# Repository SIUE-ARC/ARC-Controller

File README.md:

# ARC-Controller
A PSoC4 based robotics control board.

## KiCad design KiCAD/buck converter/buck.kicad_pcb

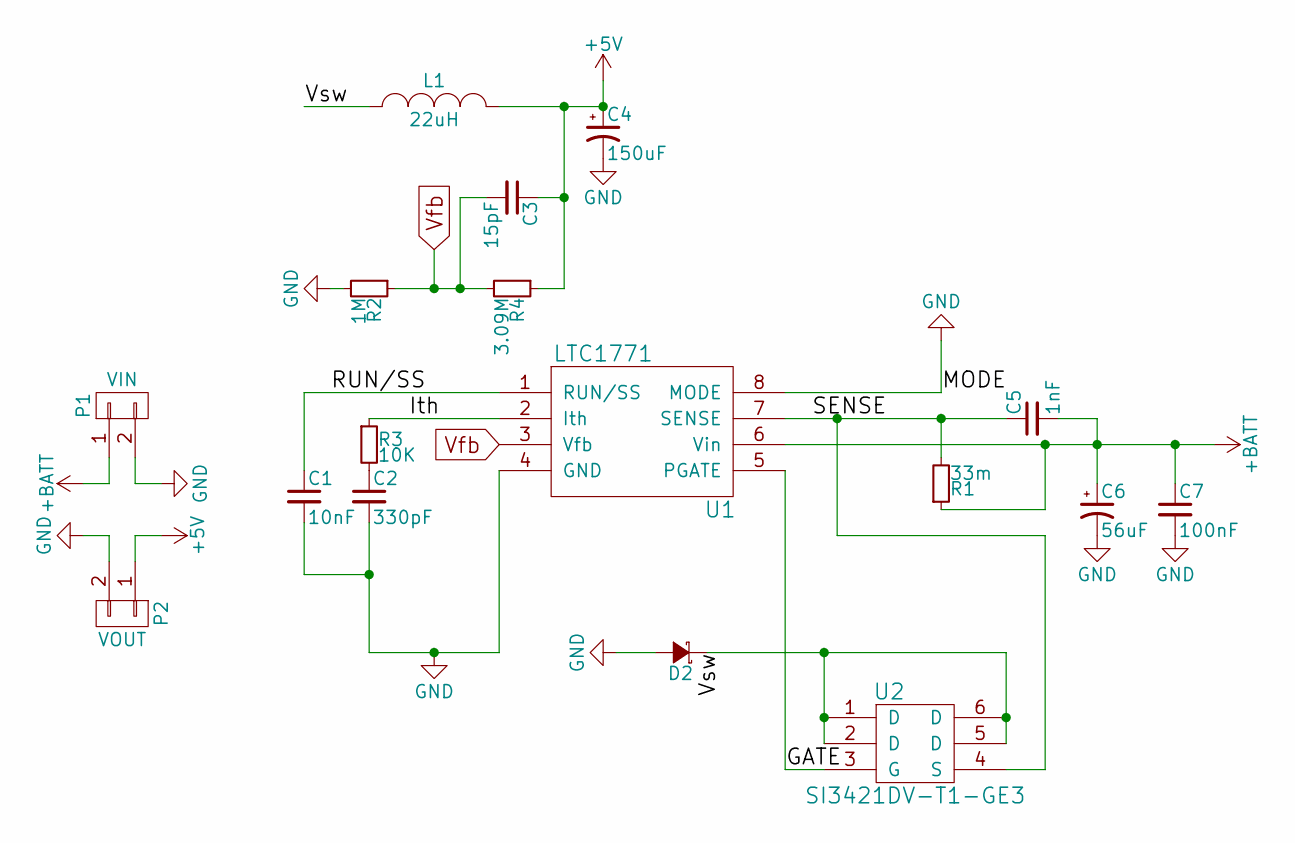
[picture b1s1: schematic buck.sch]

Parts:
C1: 10nF; C_0805_HandSoldering
C2: 330pF; C_0805_HandSoldering
C3: 15pF; C_0805_HandSoldering
C4: 150uF; CP_Elec_6.3x7.7
C5: 1nF; C_0805_HandSoldering
C6: 56uF; CP_Elec_5x5.7
C7: 100nF; C_0805_HandSoldering
D2: D_Schottky_Small; D_SMA_Handsoldering
L1: 22uH; 14mm-Inductor
P1: VIN; TerminalBlock_Pheonix_PT-3.5mm_2pol
P2: VOUT; TerminalBlock_Pheonix_PT-3.5mm_2pol
R1: 33m; R_1206_HandSoldering
R2: 1M; R_0805_HandSoldering
R3: 10K; R_0805_HandSoldering
R4: 3.09M; R_0805_HandSoldering
U1: LTC1771; SOIC-8_3.9x4.9mm_Pitch1.27mm
U2: SI3421DV-T1-GE3; SOT-23-6_Handsoldering

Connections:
+5V: C3.1, C4.1, L1.2, P2.1, R4.1
+BATT: C5.2, C6.1, C7.1, P1.1, R1.1, U1.6 (Vin)
/GATE: U1.5 (PGATE), U2.3 (G)
/Ith: R3.1, U1.2 (Ith)
/RUN/SS: C1.1, U1.1 (RUN/SS)
/SENSE: C5.1, R1.2, U1.7 (SENSE), U2.4 (S)
/Vsw: D2.1 (K), L1.1, U2.1 (D), U2.2 (D), U2.5 (D), U2.6 (D)
GND: C1.2, C2.2, C4.2, C6.2, C7.2, D2.2 (A), P1.2, P2.2, R2.2, U1.4 (GND), U1.8 (MODE)
unnamed: C2.1, R3.2
Vfb: C3.2, R2.1, R4.2, U1.3 (Vfb)

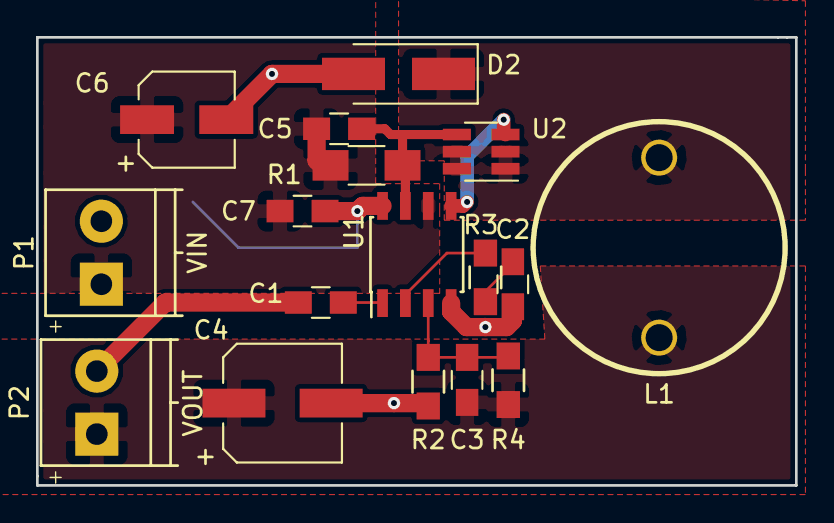
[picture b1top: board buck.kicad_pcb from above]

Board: 2 copper layers, 42.2 x 24.9 mm, 17 parts (0 on the bottom side), 10 nets.

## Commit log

2017-01-12 Added all of my previous work to the repo
2017-01-18 changed redundant heirarchy.
2017-01-18 Update PSoC hardware configurations
2017-01-18 Updated .gitignore to exclude generated source
2017-01-20 Updated hardware config for more ADC inputs and I2C support
2017-01-20 Updated hardware configuration
2017-02-05 Designed a buck converter to test for use in the controller
2017-02-06 Added LTSpice schematic
2017-02-06 Improved the buck converter board layout
2017-02-06 Improved silk screen
2017-02-06 Added BOM
2017-02-06 Finished PCB layout for buck converter
2017-02-06 Updated copper pour size of +BAT net
2017-02-06 Updated silk
2017-02-06 Fixed capacitor silk
2017-02-06 Updated board layout
2017-02-08 Added work checklist
2017-02-09 test
2017-02-09 test2
2017-02-09 Started development of UART. Transmit and Receive functions under test
2017-02-09 Ooops forgot to track external source
2017-02-14 UART under test. Reading bad data.
2017-02-28 Debugging UART
2017-03-10 Updated inductor footprint
2017-03-10 Added new inductor library to repo
2017-03-10 Moved a track that was a tad close for comfort
2017-03-14 UART fixed
2017-03-24 Updated schematic, PCB, amd BOM
2017-03-24 Updated spice
2017-03-24 Updated PCB and SPICE
2017-03-28 Added motor functionality. Need to test
2017-03-28 Updated workspace to cleanup hardware schematics
2017-04-02 Board design updated
2017-04-04 Updated commands
2017-04-04 Motors can be driven!
2017-04-06 Servo control working
2017-04-07 Updated comments
2017-04-10 Ooops, forgot to push all the source files besides main and comm
2017-04-12 Started Analog and DMA stuff. All needs tested.
2017-04-12 Moved to new Firmware branch
2017-04-13 Added PID control algorithm. Needs to be tested.
2017-04-13 dunno what changed but Creator said something was modified and I am not taking risks
2017-04-13 git complaining about shit
2017-04-13 updated board with via stitching
2017-04-13 kicad said i changed something earlier. i didnt wanna disagree
2017-04-14 Not working :(
2017-04-25 Dunno what these are but im commiting them
